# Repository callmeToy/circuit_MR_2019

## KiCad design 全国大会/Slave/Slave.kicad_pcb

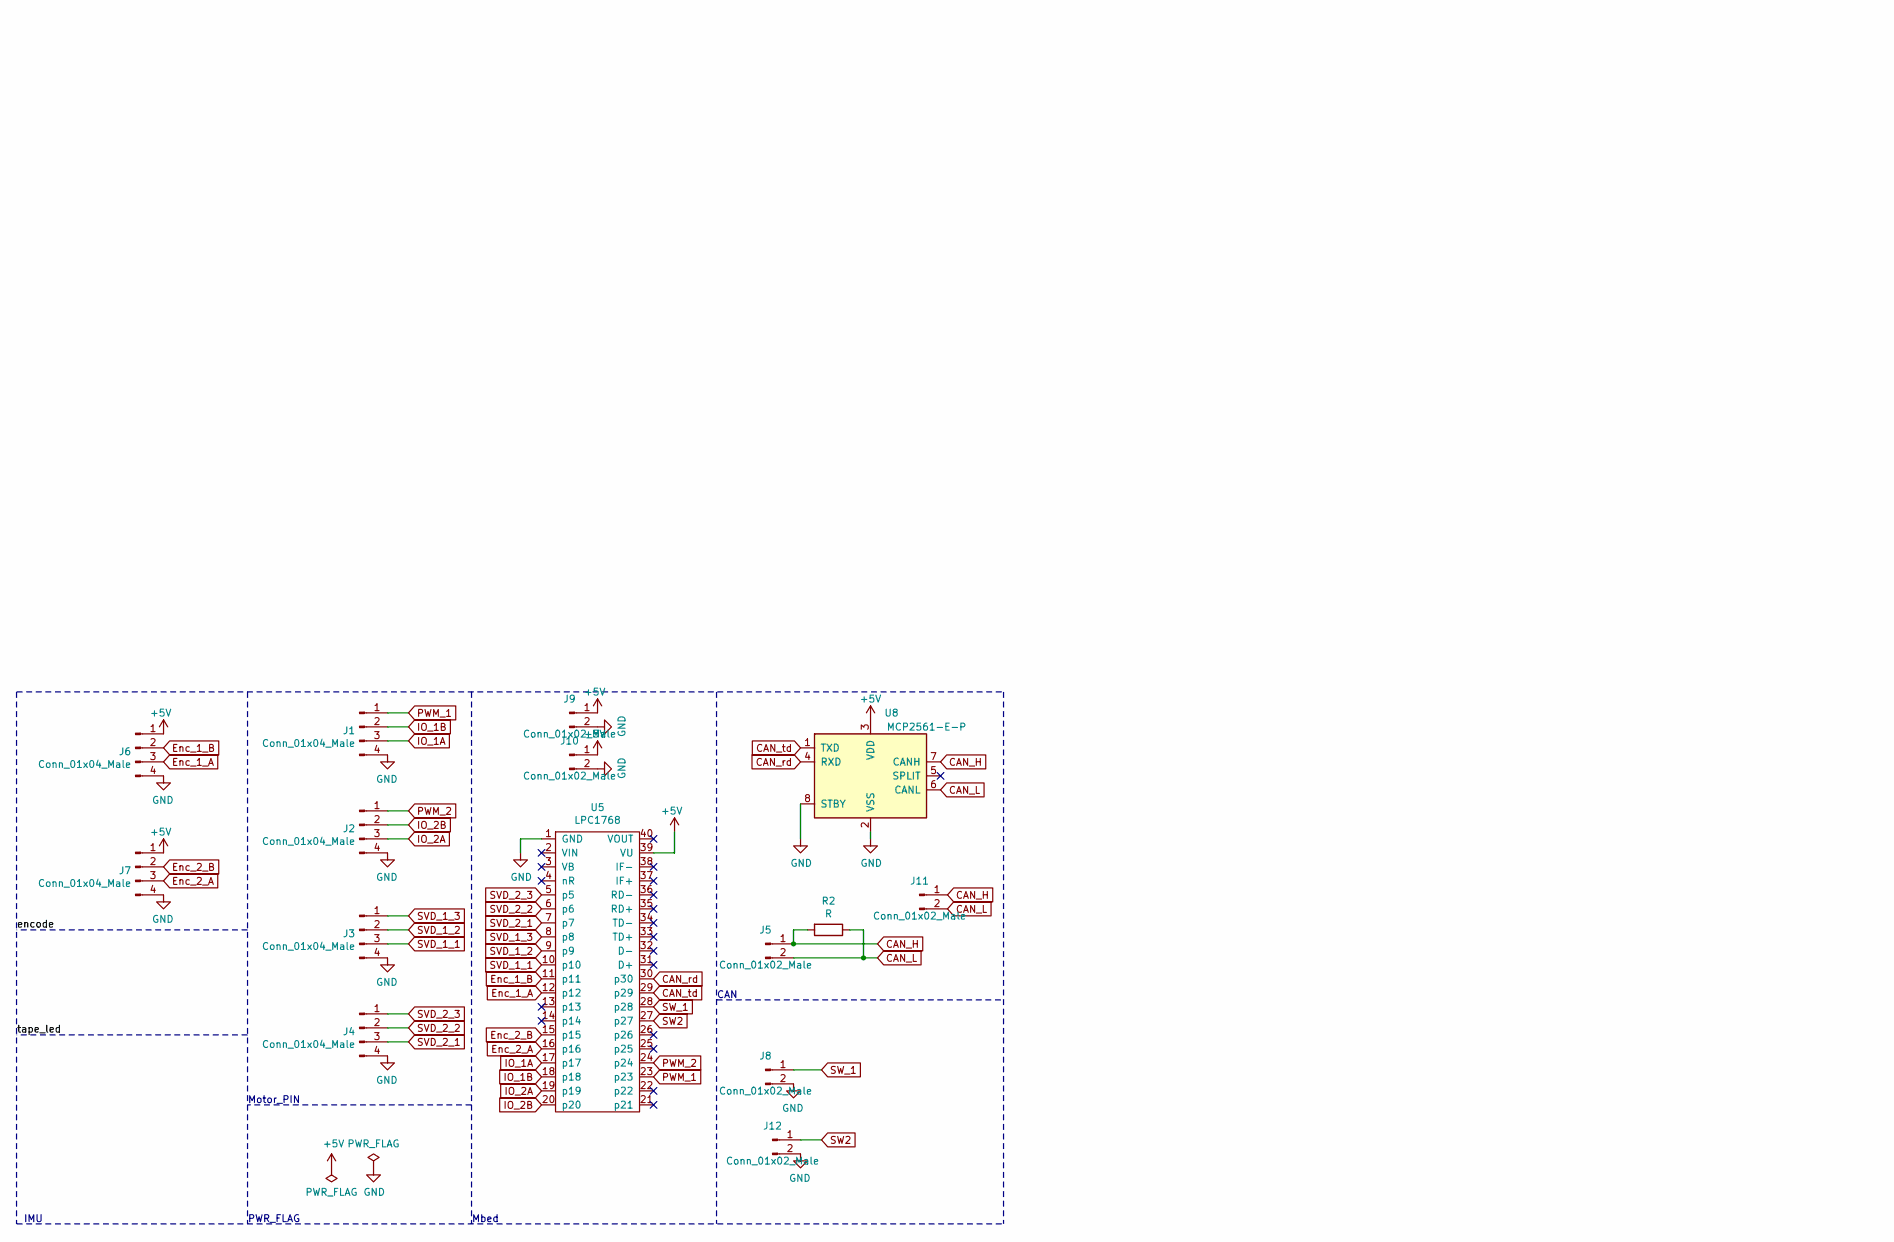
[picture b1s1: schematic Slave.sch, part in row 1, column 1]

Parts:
J1, J2, J3, J4, J6, J7: Conn_01x04_Male; JST_XH_S4B-XH-A_1x04_P2.50mm_Horizontal
J5, J8, J9, J10, J11, J12: Conn_01x02_Male; JST_XH_S2B-XH-A_1x02_P2.50mm_Horizontal
R2: R; R_Axial_DIN0207_L6.3mm_D2.5mm_P7.62mm_Horizontal
U5: LPC1768
U8: MCP2561-E-P; DIP-8_W7.62mm

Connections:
+5V: J6.1, J7.1, J9.1, J10.1, U5.39 (VU), U8.3 (VDD)
CAN_H: J5.1, J11.1, R2.2, U8.7 (CANH)
CAN_L: J5.2, J11.2, R2.1, U8.6 (CANL)
CAN_rd: U5.30 (p30), U8.4 (RXD)
CAN_td: U5.29 (p29), U8.1 (TXD)
Enc_1_A: J6.3, U5.12 (p12)
Enc_1_B: J6.2, U5.11 (p11)
Enc_2_A: J7.3, U5.16 (p16)
Enc_2_B: J7.2, U5.15 (p15)
GND: J1.4, J2.4, J3.4, J4.4, J6.4, J7.4, J8.2, J9.2, J10.2, J12.2, U5.1 (GND), U8.2 (VSS), U8.8 (STBY)
IO_1A: J1.3, U5.17 (p17)
IO_1B: J1.2, U5.18 (p18)
IO_2A: J2.3, U5.19 (p19)
IO_2B: J2.2, U5.20 (p20)
PWM_1: J1.1, U5.23 (p23)
PWM_2: J2.1, U5.24 (p24)
SVD_1_1: J3.3, U5.10 (p10)
SVD_1_2: J3.2, U5.9 (p9)
SVD_1_3: J3.1, U5.8 (p8)
SVD_2_1: J4.3, U5.7 (p7)
SVD_2_2: J4.2, U5.6 (p6)
SVD_2_3: J4.1, U5.5 (p5)
SW2: J12.1, U5.27 (p27)
SW_1: J8.1, U5.28 (p28)

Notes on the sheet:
CAN
Mbed
IMU
PWR_FLAG
Motor_PIN

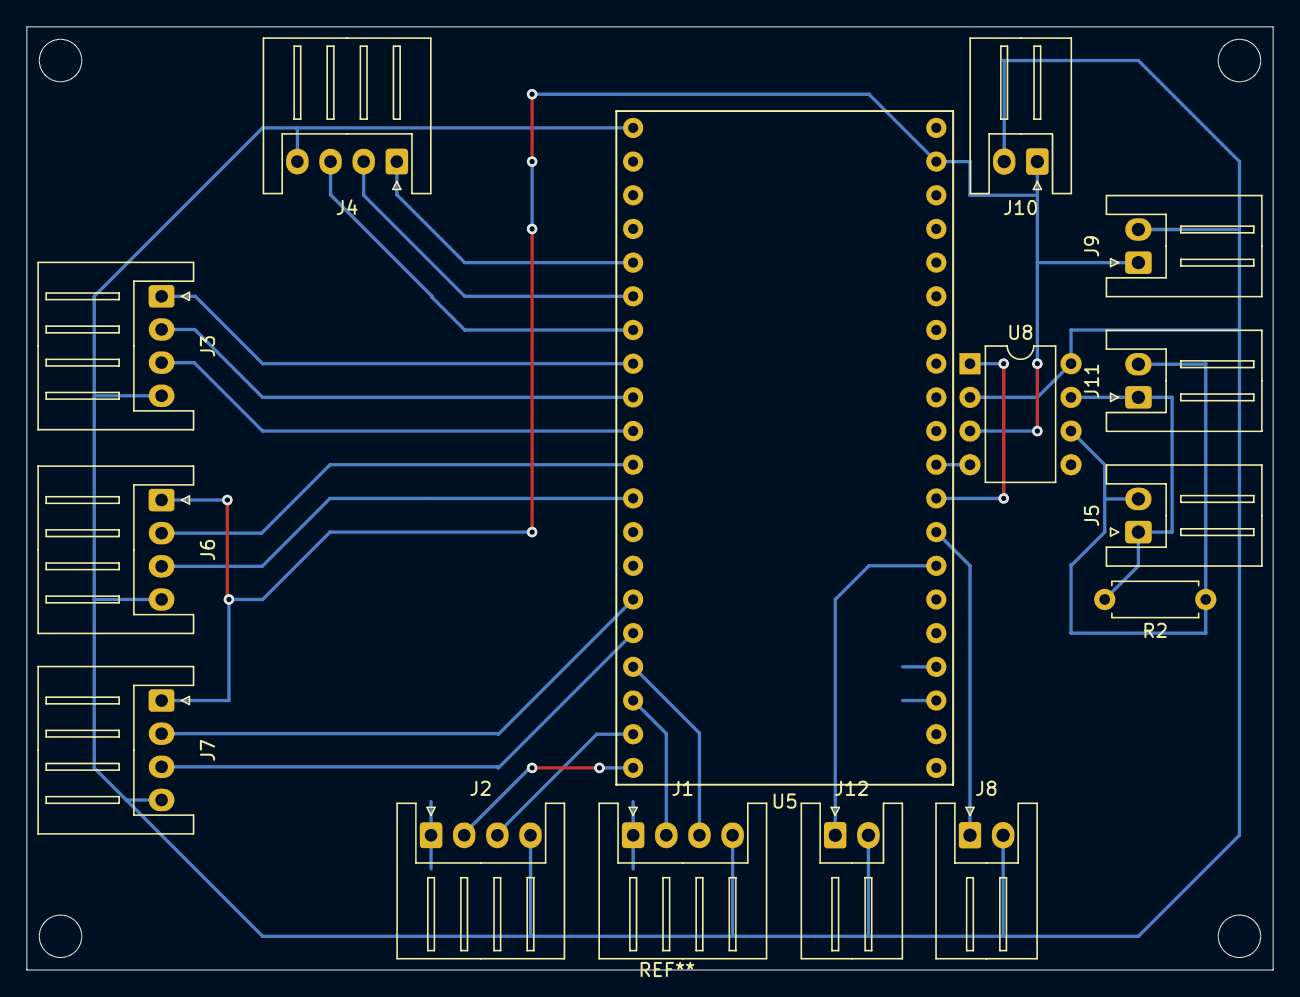
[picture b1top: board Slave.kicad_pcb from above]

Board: 2 copper layers, 94.0 x 71.1 mm, 15 parts (0 on the bottom side), 24 nets.

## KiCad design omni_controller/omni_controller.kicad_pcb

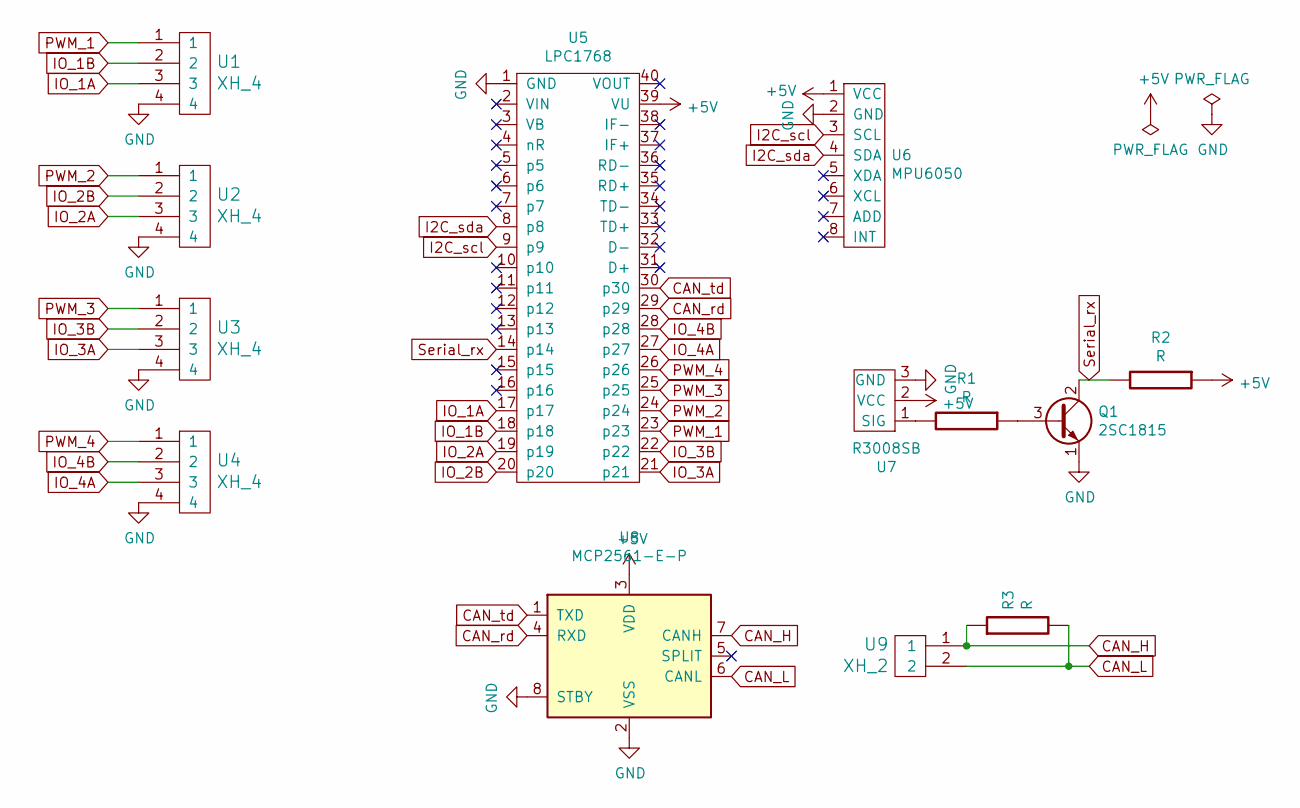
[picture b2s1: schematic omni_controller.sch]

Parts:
Q1: 2SC1815; TO-92_Inline
R1, R2, R3: R; R_Axial_DIN0207_L6.3mm_D2.5mm_P7.62mm_Horizontal
U1, U2, U3, U4: XH_4; JST_XH_S04B-XH-A_04x2.50mm_Angled
U5: LPC1768
U6: MPU6050
U7: R3008SB
U8: MCP2561-E-P; DIP-8_W7.62mm
U9: XH_2; JST_XH_S02B-XH-A_02x2.50mm_Angled

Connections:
+5V: R2.1, U5.39 (VU), U6.1 (VCC), U7.2 (VCC), U8.3 (VDD)
CAN_H: R3.1, U8.7 (CANH), U9.1
CAN_L: R3.2, U8.6 (CANL), U9.2
CAN_rd: U5.29 (p29), U8.4 (RXD)
CAN_td: U5.30 (p30), U8.1 (TXD)
GND: Q1.1 (E), U1.4, U2.4, U3.4, U4.4, U5.1 (GND), U6.2 (GND), U7.3 (GND), U8.2 (VSS), U8.8 (STBY)
I2C_scl: U5.9 (p9), U6.3 (SCL)
I2C_sda: U5.8 (p8), U6.4 (SDA)
IO_1A: U1.3, U5.17 (p17)
IO_1B: U1.2, U5.18 (p18)
IO_2A: U2.3, U5.19 (p19)
IO_2B: U2.2, U5.20 (p20)
IO_3A: U3.3, U5.21 (p21)
IO_3B: U3.2, U5.22 (p22)
IO_4A: U4.3, U5.27 (p27)
IO_4B: U4.2, U5.28 (p28)
unnamed: Q1.3 (B), R1.1
unnamed: R1.2, U7.1 (SIG)
PWM_1: U1.1, U5.23 (p23)
PWM_2: U2.1, U5.24 (p24)
PWM_3: U3.1, U5.25 (p25)
PWM_4: U4.1, U5.26 (p26)
Serial_rx: Q1.2 (C), R2.2, U5.14 (p14)

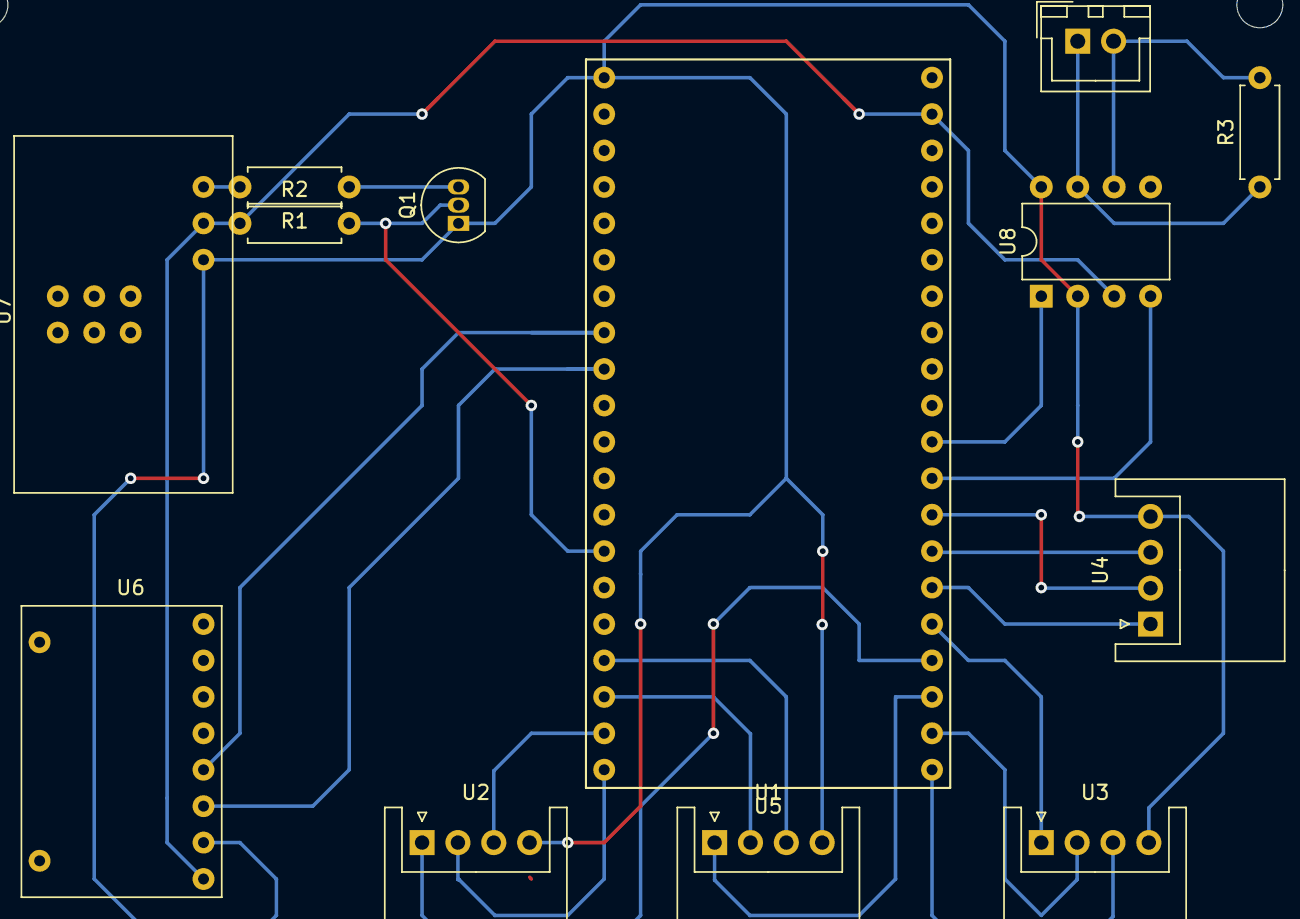
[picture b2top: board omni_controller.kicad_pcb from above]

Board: 2 copper layers, 13 parts (0 on the bottom side), 23 nets.

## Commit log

2019-07-09 add: オムニコントローラの追加
2019-07-10 update: ライブラリの更新
2019-08-16 update: 本番用に変更
2019-08-16 update:MR1の基板完成
2019-08-16 update:MR2の基板完成
2019-08-17 update:XHを変更
2019-08-20 fix: MR1
2019-09-03 update: 加工用データ
2019-09-08 update:設計変更に伴う改修、CAN通信周りの不具合を修正
2019-09-13 update : mr1:sub_swの追加 mr2:エンコーダーの増設
2019-09-13 add:仕様書のようなもの
2019-10-24 add: 加工用データ
2019-10-24 update: 全国大会用Master基板
2019-10-25 update: 全国大会用Slave基板
2019-10-25 update: 全国大会用加工データ
